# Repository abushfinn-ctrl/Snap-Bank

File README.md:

# Snap-Bank
A powerbank with a removable 18650 battery for quick "charges" on the go. I love the idea of this project because it allows you to only carry an extra or two 18650 batteries instead of having to carry a massive powerbank. This means that at school or scout camps I can keep a small powerbank in my pocket because I have really bad battery life on my phone, and I can still have the capacity of a 4 cell powerbank when I need via switching the batteries out. I also designed it that the battery holding can come fully out so you could carry an extra 18650 in the battery holder to keep it a little more protected, although I will probably end up printing a screw on case for the batteries. I also made it with a clear acrylic panel so I can see the cool internals that I spent time on.
# Final Product

# Pictures and Renders

# PCB

# BOM
|Part Number                |Manufacturer Part Number|Description                     |Quantity|Unit Price CAD|Total Price CAD|Running total CAD|Unit Price USD|Total Price USD|Running total USD|Links                                                                                                                                                                                                                                                                                                                                                                                                                                                                                                                                                                                                                                                                                                                                                          |
|---------------------------|------------------------|--------------------------------|--------|--------------|---------------|-----------------|--------------|---------------|-----------------|---------------------------------------------------------------------------------------------------------------------------------------------------------------------------------------------------------------------------------------------------------------------------------------------------------------------------------------------------------------------------------------------------------------------------------------------------------------------------------------------------------------------------------------------------------------------------------------------------------------------------------------------------------------------------------------------------------------------------------------------------------------|
|1276-1096-1-ND             |CL21A106KOQNNNE         |CAP CER 10UF 16V X5R 0805       |10      |$0.08         |$0.78          |$0.78            |$0.06         |$0.57          |$0.57            |https://www.digikey.ca/en/products/detail/samsung-electro-mechanics/CL21A106KOQNNNE/3886754                                                                                                                                                                                                                                                                                                                                                                                                                                                                                                                                                                                                                                                                    |
|1276-2909-1-ND             |CL21A226MOQNNNE         |CAP CER 22UF 16V X5R 0805       |5       |$0.39         |$1.95          |$2.73            |$0.28         |$1.42          |$1.98            |https://www.digikey.ca/en/products/detail/samsung-electro-mechanics/CL21A226MOQNNNE/3888567                                                                                                                                                                                                                                                                                                                                                                                                                                                                                                                                                                                                                                                                    |
|311-2.0ARCT-ND             |RC0805JR-072RL          |RES 2 OHM 5% 1/8W 0805          |4       |$0.15         |$0.60          |$3.33            |$0.11         |$0.44          |$2.42            |https://www.digikey.ca/en/products/detail/yageo/RC0805JR-072RL/728267                                                                                                                                                                                                                                                                                                                                                                                                                                                                                                                                                                                                                                                                                          |
|311-20ARCT-ND              |RC0805JR-0720RL         |RES 20 OHM 5% 1/8W 0805         |2       |$0.15         |$0.30          |$3.63            |$0.11         |$0.22          |$2.64            |https://www.digikey.ca/en/products/detail/yageo/RC0805JR-0720RL/728281                                                                                                                                                                                                                                                                                                                                                                                                                                                                                                                                                                                                                                                                                         |
|311-10KARCT-ND             |RC0805JR-0710KL         |RES 10K OHM 5% 1/8W 0805        |2       |$0.15         |$0.30          |$3.93            |$0.11         |$0.22          |$2.86            |https://www.digikey.ca/en/products/detail/yageo/RC0805JR-0710KL/728241                                                                                                                                                                                                                                                                                                                                                                                                                                                                                                                                                                                                                                                                                         |
|311-5.1KARCT-ND            |RC0805JR-075K1L         |RES 5.1K OHM 5% 1/8W 0805       |10      |$0.05         |$0.45          |$4.38            |$0.03         |$0.33          |$3.18            |https://www.digikey.ca/en/products/detail/yageo/RC0805JR-075K1L/728338                                                                                                                                                                                                                                                                                                                                                                                                                                                                                                                                                                                                                                                                                         |
|2073-USB4085-GF-ACT-ND     |USB4085-GF-A            |CONN RCPT USB2.0 TYPE C 16+8POS |2       |$1.31         |$2.62          |$7.00            |$0.95         |$1.90          |$5.09            |https://www.digikey.ca/en/products/detail/gct/USB4085-GF-A/9859662                                                                                                                                                                                                                                                                                                                                                                                                                                                                                                                                                                                                                                                                                             |
|587-LAXHG6060YEL1R0NMRCT-ND|LAXHG6060YEL1R0NMR      |FIXED IND 1UH 6.2A 13 MOHM SMD  |2       |$0.95         |$1.90          |$8.90            |$0.69         |$1.38          |$6.47            |https://www.digikey.ca/en/products/detail/taiyo-yuden/LAXHG6060YEL1R0NMR/17831610                                                                                                                                                                                                                                                                                                                                                                                                                                                                                                                                                                                                                                                                              |
|EG5350CT-ND                |TL3305AF160QG           |SWITCH TACTILE SPST-NO 0.05A 12V|2       |$0.31         |$0.62          |$9.52            |$0.23         |$0.45          |$6.92            |https://www.digikey.ca/en/products/detail/e-switch/TL3305AF160QG/5816181                                                                                                                                                                                                                                                                                                                                                                                                                                                                                                                                                                                                                                                                                       |
|N/A                        |Digikey Shipping        |Shipping for digikey            |1       |$8.00         |$8.00          |$17.52           |$5.82         |$5.82          |$12.74           |                                                                                                                                                                                                                                                                                                                                                                                                                                                                                                                                                                                                                                                                                                                                                               |
|N/A                        |HST                     |Taxes for Digikey               |1       |$2.28         |$2.28          |$19.80           |$1.66         |$1.66          |$14.40           |                                                                                                                                                                                                                                                                                                                                                                                                                                                                                                                                                                                                                                                                                                                                                               |
|IP5306                     |Aliexpress              |IP5306 from aliexpress (10 Pack)|1       |3.47          |3.47           |$23.27           |$2.52         |$2.52          |$16.92           |https://www.aliexpress.com/item/1005006842113401.html?spm=a2g0o.detail.0.0.283cSR31SR31nH&mp=1&pdp_npi=6%40dis%21CAD%21CAD+3.47%21CAD+3.47%21%21CAD+3.47%21%21%21%40210328db17789544691373336e2759%2112000038485079092%21ct%21CA%217508201891%21%211%210%21                                                                                                                                                                                                                                                                                                                                                                                                                                                                                                    |
|18650                      |Aliexpress              |INR18650 25R 1865 2500Mah (4 Pack)|1       |19.66         |19.66          |$42.93           |$14.29        |$14.29         |$31.21           |https://www.aliexpress.com/item/1005009553868764.html?spm=a2g0o.productlist.main.8.77c47db5yCfoUb&algo_pvid=2f68f18d-1428-4b6b-b710-f3b88832853b&aem_p4p_detail=202605161116164352526642951040001402992&algo_exp_id=2f68f18d-1428-4b6b-b710-f3b88832853b-7&pdp_ext_f=%7B%22order%22%3A%22332%22%2C%22eval%22%3A%221%22%2C%22fromPage%22%3A%22search%22%7D&pdp_npi=6%40dis%21CAD%21137.05%2160.30%21%21%21662.40%21291.46%21%402103274e17789553766967088e9a6b%2112000049447230182%21sea%21CA%217508201891%21X%211%210%21n_tag%3A-29911%3Bd%3Acb3b2026%3Bm03_new_user%3A-29895&curPageLogUid=VhiCHPXzVzso&utparam-url=scene%3Asearch%7Cquery_from%3A%7Cx_object_id%3A1005009553868764%7C_p_origin_prod%3A&search_p4p_id=202605161116164352526642951040001402992_2|

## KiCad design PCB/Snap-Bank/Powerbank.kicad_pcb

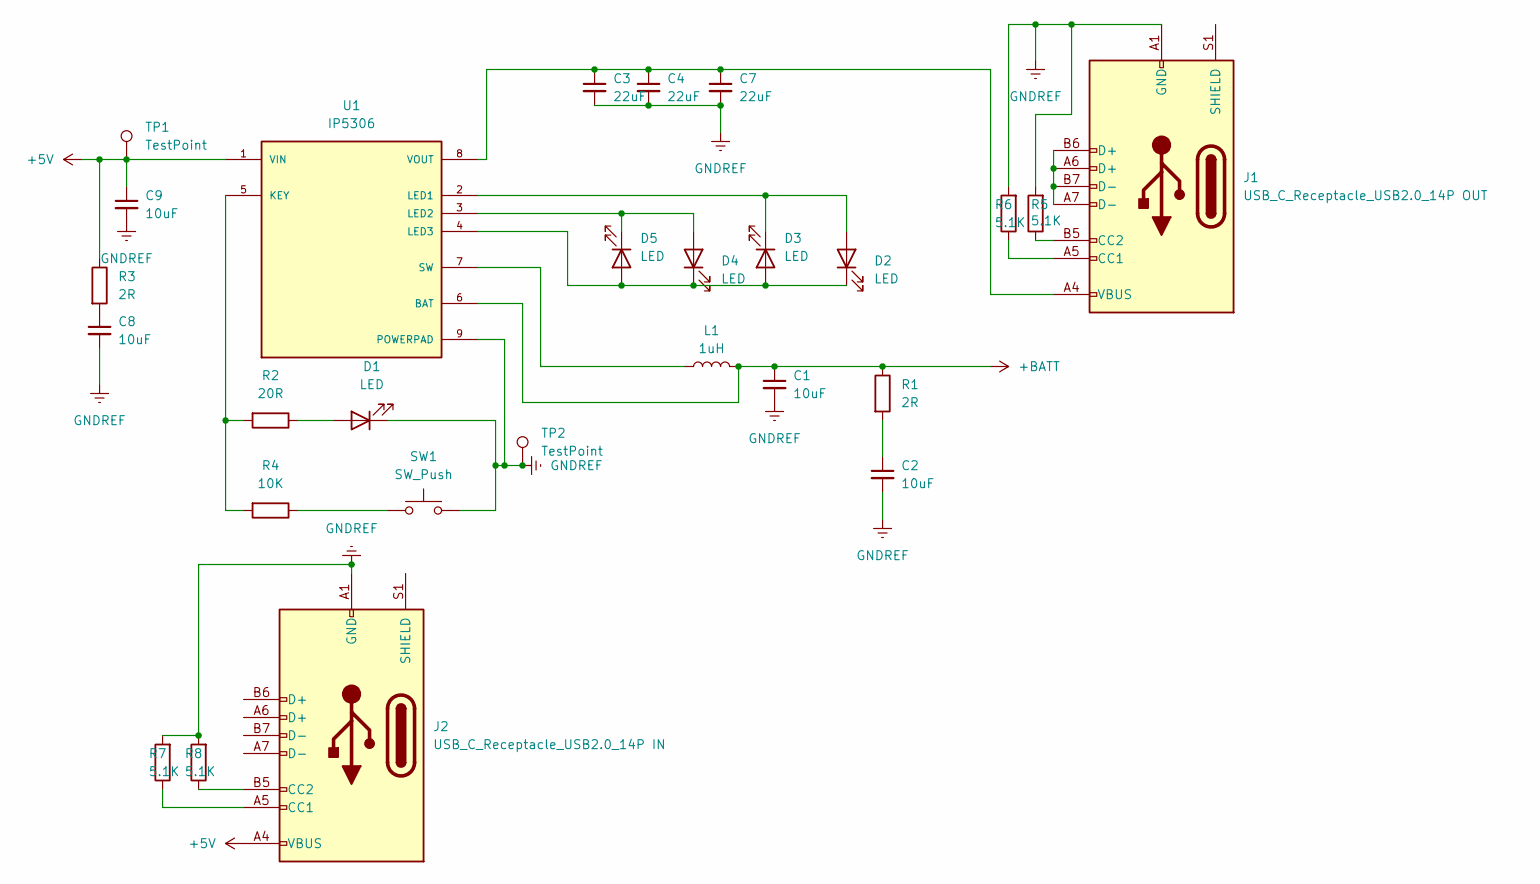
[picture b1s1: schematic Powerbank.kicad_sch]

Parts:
C1, C2, C8, C9: 10uF; R_0805_2012Metric
C3, C4, C7: 22uF; R_0805_2012Metric
D1, D2, D3, D4, D5: LED; LED_0805_2012Metric
J1: USB_C_Receptacle_USB2.0_14P OUT; USB_C_Receptacle_GCT_USB4085
J2: USB_C_Receptacle_USB2.0_14P IN; USB_C_Receptacle_GCT_USB4085
L1: 1uH; L_Chilisin_BWVS00606020
R1, R3: 2R; R_0805_2012Metric
R2: 20R; R_0805_2012Metric
R4: 10K; R_0805_2012Metric
R5, R6, R7, R8: 5.1K; R_0805_2012Metric
SW1: SW_Push; SW_SPST_TL3305A
TP1, TP2: TestPoint; TestPoint_Pad_D2.0mm
U1: IP5306; SOP127P600X165-9N; PARTREV 1.31

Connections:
+5V: C9.1, J2.A4 (VBUS), J2.A9 (VBUS), J2.B4 (VBUS), J2.B9 (VBUS), R3.1, TP1.1, U1.1 (VIN)
+BATT: C1.1, L1.2, R1.1, U1.6 (BAT)
GNDREF: C1.2, C2.2, C3.2, C4.2, C7.2, C8.2, C9.2, D1.1 (K), J1.A1 (GND), J1.A12 (GND), J1.B1 (GND), J1.B12 (GND), J2.A1 (GND), J2.A12 (GND), J2.B1 (GND), J2.B12 (GND), R5.2, R6.2, R7.2, R8.2, SW1.2, TP2.1, U1.9 (POWERPAD)
unnamed: C2.1, R1.2
unnamed: C8.1, R3.2
unnamed: D1.2 (A), R2.1
unnamed: D2.2 (A), D3.1 (K), U1.2 (LED1)
unnamed: D2.1 (K), D3.2 (A), D4.1 (K), D5.2 (A), U1.4 (LED3)
unnamed: D4.2 (A), D5.1 (K), U1.3 (LED2)
unnamed: J1.A5 (CC1), R6.1
unnamed: J1.B5 (CC2), R5.1
unnamed: J1.A6 (D+), J1.A7 (D-), J1.B6 (D+), J1.B7 (D-)
unnamed: J2.A5 (CC1), R7.1
unnamed: J2.B5 (CC2), R8.1
unnamed: R4.1, SW1.1
unnamed: R2.2, R4.2, U1.5 (KEY)
unnamed: L1.1, U1.7 (SW)
unnamed: C3.1, C4.1, C7.1, J1.A4 (VBUS), J1.A9 (VBUS), J1.B4 (VBUS), J1.B9 (VBUS), U1.8 (VOUT)

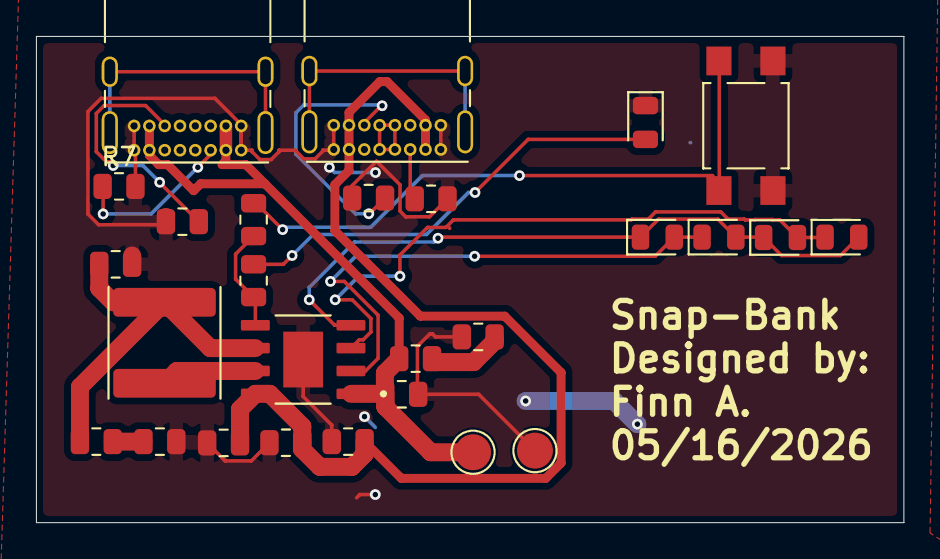
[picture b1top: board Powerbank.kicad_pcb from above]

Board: 2 copper layers, 48.2 x 27.0 mm, 27 parts (0 on the bottom side), 18 nets.
